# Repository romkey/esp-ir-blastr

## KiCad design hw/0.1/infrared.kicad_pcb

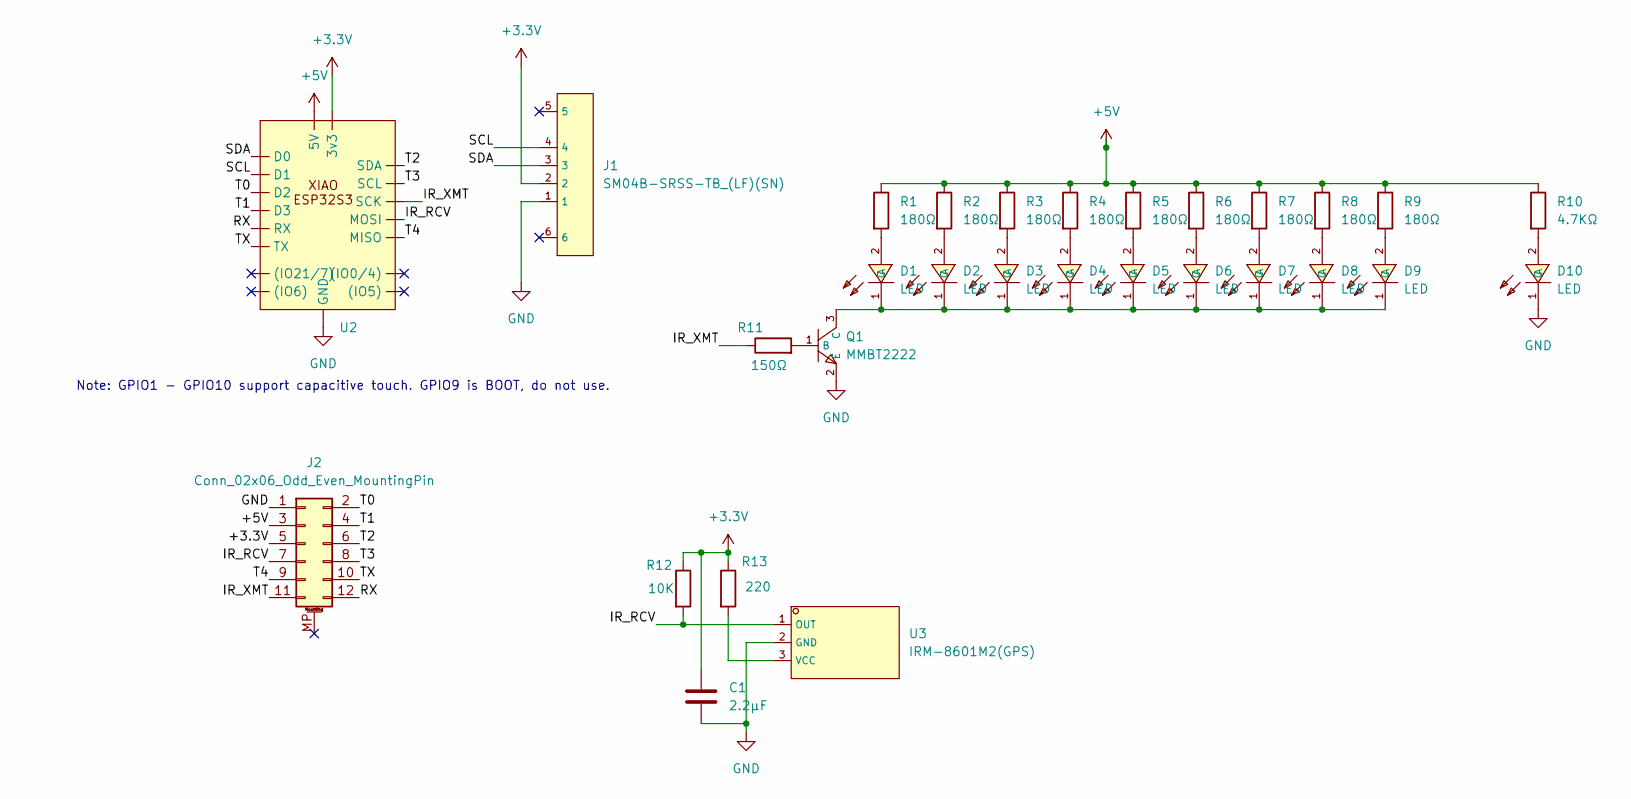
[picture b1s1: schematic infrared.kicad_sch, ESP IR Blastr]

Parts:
C1: 2.2µF; C_0805_2012Metric; LCSC C19110
D1, D2, D3, D4, D5, D6, D7, D8: LED; SENSOR-SMD_L3.2-W2.4-R-FD; LCSC C131198
D9: LED; LED_0805_2012Metric; LCSC C2297
D10: LED; LED_0805_2012Metric; LCSC C84256
J1: SM04B-SRSS-TB_(LF)(SN); CONN-SMD_4P-P1.00_SM04B-SRSS-TB-LF-SN; LCSC C160404
J2: Conn_02x06_Odd_Even_MountingPin; PinHeader_2x06_P2.54mm_Vertical
Q1: MMBT2222; SOT-23-3_L2.9-W1.4-P1.91-LS2.6-BR; LCSC C2891810
R1, R2, R3, R4, R5, R6, R7, R8: 180Ω; R_0805_2012Metric_Pad1.20x1.40mm_HandSolder; LCSC C25270
R9: 180Ω; R_0805_2012Metric; LCSC C25270
R10: 4.7KΩ; R_0805_2012Metric; LCSC C17673
R11: 150Ω; R_0805_2012Metric_Pad1.20x1.40mm_HandSolder; LCSC C17471
R12: 10K; R_0805_2012Metric; LCSC C17414
R13: 220; R_0805_2012Metric; LCSC C17557
U2: Xiao ESP32S3 PLUS
U3: IRM-8601M2(GPS); SENSOR-TH_IRM-8601; LCSC C131222

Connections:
+3.3V: C1.1, J1.2, J2.5, R12.1, R13.1, U2.12 (3v3)
+5V: J2.3, R1.1, R2.1, R3.1, R4.1, R5.1, R6.1, R7.1, R8.1, R9.1, R10.1, U2.14 (5V)
/IR_RCV: J2.7, R12.2, U2.11 (MOSI), U3.1 (OUT)
/IR_XMT: J2.11, R11.1, U2.9 (SCK)
/RX: J2.12, U2.8 (RX)
/SCL: J1.4, U2.2 (D1)
/SDA: J1.3, U2.1 (D0)
/T0: J2.2, U2.3 (D2)
/T1: J2.4, U2.4 (D3)
/T2: J2.6, U2.5 (SDA)
/T3: J2.8, U2.6 (SCL)
/T4: J2.9, U2.10 (MISO)
/TX: J2.10, U2.7 (TX)
GND: C1.2, D10.1 (C), J1.1, J2.1, Q1.2 (E), U2.13 (GND), U3.2 (GND)
unnamed: D1.2 (A), R1.2
unnamed: D1.1 (C), D2.1 (C), D3.1 (C), D4.1 (C), D5.1 (C), D6.1 (C), D7.1 (C), D8.1 (C), D9.1 (C), Q1.3 (C)
unnamed: D2.2 (A), R2.2
unnamed: D3.2 (A), R3.2
unnamed: D4.2 (A), R4.2
unnamed: D5.2 (A), R5.2
unnamed: D6.2 (A), R6.2
unnamed: D7.2 (A), R7.2
unnamed: D8.2 (A), R8.2
unnamed: D9.2 (A), R9.2
unnamed: D10.2 (A), R10.2
unnamed: Q1.1 (B), R11.2
unnamed: R13.2, U3.3 (VCC)

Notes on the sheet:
Note: GPIO1 - GPIO10 support capacitive touch. GPIO9 is BOOT, do not use.

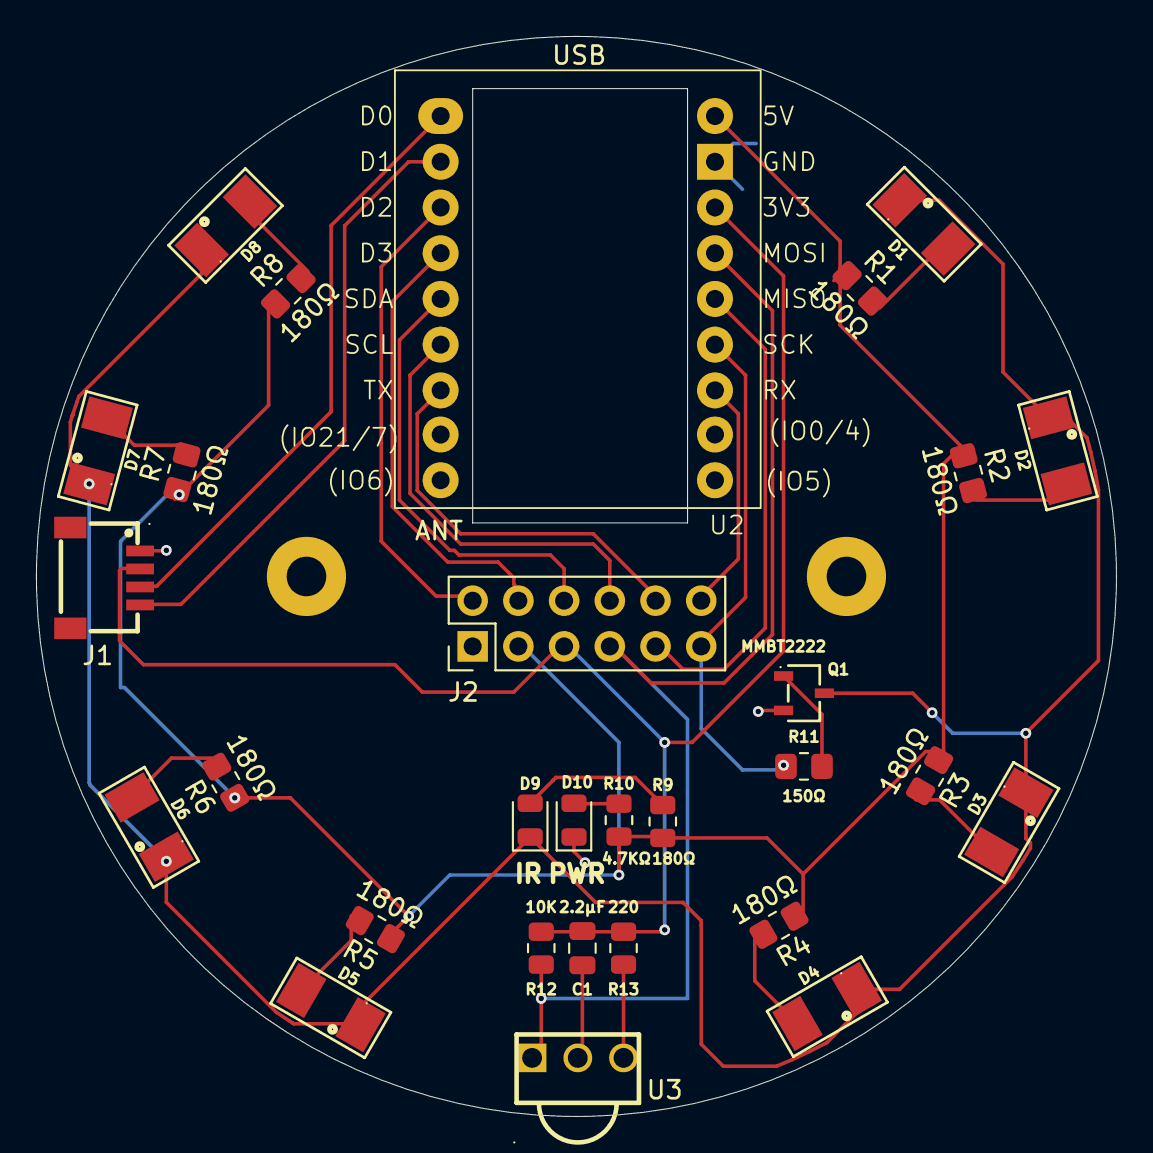
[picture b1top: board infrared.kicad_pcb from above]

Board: 2 copper layers, 60.0 x 60.0 mm, 31 parts (0 on the bottom side), 27 nets.

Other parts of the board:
MNT1: MountingHole_2.2mm_M2_Pad
MNT2: (no value)

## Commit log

2025-02-03 added hardware and datasheet
2025-02-03 added IDs to buttons
2025-02-07 fixed light actions
2025-02-07 fixed fix
2025-02-07 fix the fix again
2025-02-07 one more try
2025-02-07 should be no return value
2025-03-30 Update ir-blaster.yaml - comment out rmt_channel
